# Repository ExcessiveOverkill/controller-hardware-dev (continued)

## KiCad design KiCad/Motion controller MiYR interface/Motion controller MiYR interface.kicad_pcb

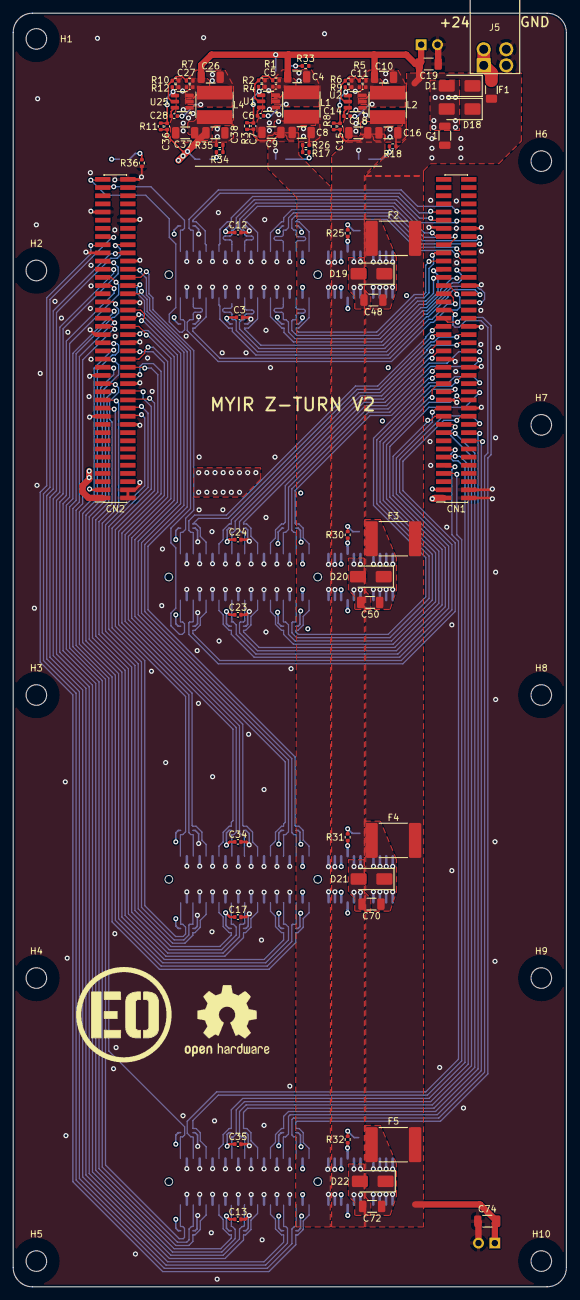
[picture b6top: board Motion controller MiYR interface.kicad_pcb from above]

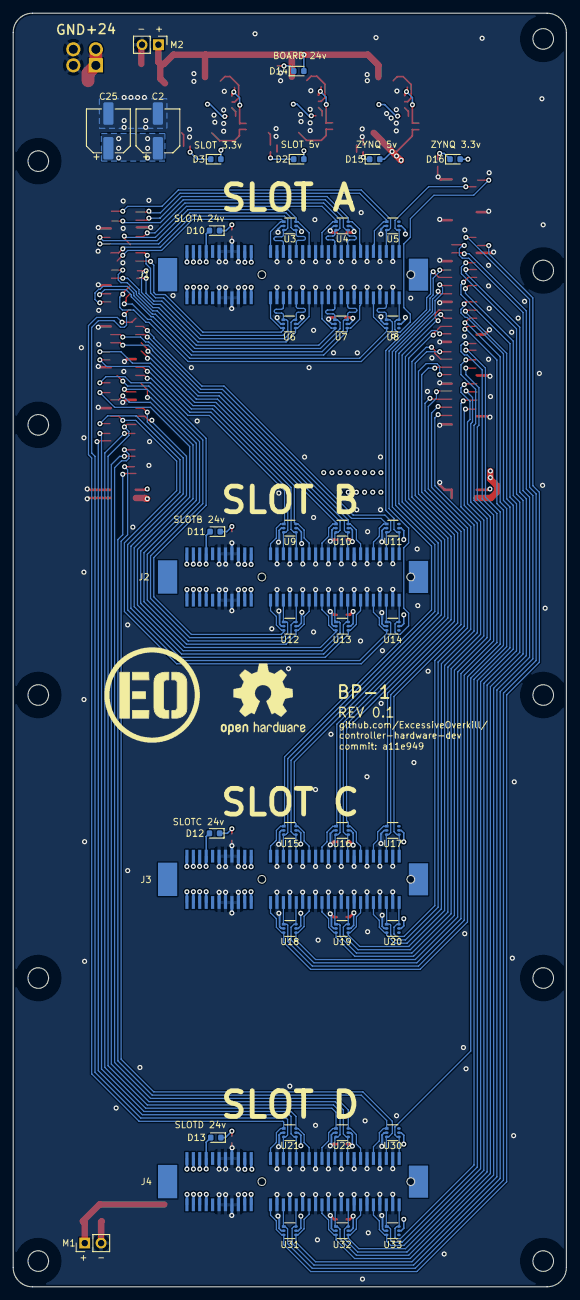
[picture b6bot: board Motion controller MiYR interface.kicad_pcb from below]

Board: 4 copper layers, 86.0 x 198.0 mm, 127 parts (41 on the bottom side), 122 nets.

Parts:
C1, C19, C48, C50, C70, C72, C74: 10uf; C_1206_3216Metric
C2, C25: 100uf; CP_Elec_6.3x7.7
C3, C5, C6, C11, C12, C13, C14, C17, C23, C24, C27, C28, C34, C35: .1uf; C_0402_1005Metric
C4, C8, C9, C10, C16, C18, C26, C37, C38: 22uf; C_1206_3216Metric
C7, C36: 75pf; C_0402_1005Metric
C15: 56pf; C_0402_1005Metric
CN1, CN2: Conn_02x40_Odd_Even; PinHeader_2x40_P1.27mm_Vertical_SMD_FLIPPED
D1, D18, D19, D20, D21, D22: SS34; D_SMA
D2, D3, D10, D11, D12, D13, D14, D15, D16: LED; LED_0603_1608Metric
F1: 10A; Fuse_1206_3216Metric
F2, F3, F4, F5: 3A; Fuse_2920_7451Metric
H1, H2, H3, H4, H5, H6, H7, H8, H9, H10: MountingHole; MountingHole_3.2mm_M3
J1, J2, J3, J4: 10061913-111PLF; PCI_64_SMD_CONNECTOR
J5: 24v; 2x02_P3.5_KF2EDGSR
L1, L2, L4: 15uH; CY54_INDUCTOR
M1, M2: Fan; PinHeader_1x02_P2.54mm_Vertical
R1, R5, R7: 500k; R_0402_1005Metric
R2, R3, R6, R8, R10, R11: 100k; R_0402_1005Metric
R4, R12, R25, R30, R31, R32, R33: 13.3k; R_0402_1005Metric
R9: 22.1k; R_0402_1005Metric
R17, R18, R26, R34, R35, R36: 1k; R_0402_1005Metric
U1, U2, U25: TPS54202DDC; SOT-23-6
U3, U4, U5, U6, U7, U8, U9, U10, U11, U12, U13, U14, U15, U16, U17, U18, U19, U20, U21, U22, U30, U31, U32, U33: D1213A-04S-7; SOT-363_DIO

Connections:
+3.3V: C3.1, C12.1, C13.1, C17.1, C23.1, C24.1, C34.1, C35.1, CN1.3, CN2.3, D16.2 (A), U3.5 (VCC), U4.5 (VCC), U5.5 (VCC), U6.5 (VCC), U7.5 (VCC), U8.5 (VCC), U9.5 (VCC), U10.5 (VCC), U11.5 (VCC), U12.5 (VCC), U13.5 (VCC), U14.5 (VCC), U15.5 (VCC), U16.5 (VCC), U17.5 (VCC), U18.5 (VCC), U19.5 (VCC), U20.5 (VCC), U21.5 (VCC), U22.5 (VCC), U30.5 (VCC), U31.5 (VCC), U32.5 (VCC), U33.5 (VCC)
+3.3VA: C15.2, C16.2, C18.2, D3.2 (A), J1.P$A10 (A10), J1.P$B10 (B10), J2.P$A10 (A10), J2.P$B10 (B10), J3.P$A10 (A10), J3.P$B10 (B10), J4.P$A10 (A10), J4.P$B10 (B10), L2.2, R8.2
+5V: C36.2, C37.2, C38.2, CN1.1, CN2.1, D15.2 (A), L4.2, R11.2
+5VA: C7.2, C8.2, C9.2, D2.2 (A), J1.P$A11 (A11), J1.P$B11 (B11), J2.P$A11 (A11), J2.P$B11 (B11), J3.P$A11 (A11), J3.P$B11 (B11), J4.P$A11 (A11), J4.P$B11 (B11), L1.2, R3.2
+24V: C1.1, C2.1, C4.2, C5.2, C10.2, C11.2, C19.1, C25.1, C26.2, C27.2, C74.1, D1.1 (K), D14.2 (A), D18.1 (K), F1.2, F2.1, F3.1, F4.1, F5.1, M1.1 (+), M2.1 (+), R1.2, R5.2, R7.2, U1.3 (VIN), U2.3 (VIN), U25.3 (VIN)
GND: C1.2, C2.2, C3.2, C4.1, C5.1, C8.1, C9.1, C10.1, C11.1, C12.2, C13.2, C16.1, C17.2, C18.1, C19.2, C23.2, C24.2, C25.2, C26.1, C27.1, C34.2, C35.2, C37.1, C38.1, C48.2, C50.2, C70.2, C72.2, C74.2, CN1.2, CN1.4, CN1.24, CN1.25, CN1.34, CN1.35, CN1.44, CN1.54, CN1.67, CN1.68, CN2.2, CN2.4, CN2.20, CN2.21, CN2.30, CN2.31, CN2.40, CN2.41, CN2.50, CN2.60, CN2.61, CN2.70, CN2.71, CN2.80, D1.2 (A), D18.2 (A), D19.2 (A), D20.2 (A), D21.2 (A), D22.2 (A), J1.P$A6 (A6), J1.P$A7 (A7), J1.P$A8 (A8), J1.P$A9 (A9), J1.P$A13 (A13), J1.P$A15 (A15), J1.P$A17 (A17), J1.P$A19 (A19), J1.P$A21 (A21), J1.P$A23 (A23), J1.P$A25 (A25), J1.P$A27 (A27), J1.P$A29 (A29), J1.P$A31 (A31), J1.P$B6 (B6), J1.P$B7 (B7), J1.P$B8 (B8), J1.P$B9 (B9), J1.P$B13 (B13), J1.P$B15 (B15), J1.P$B17 (B17), J1.P$B19 (B19), J1.P$B21 (B21), J1.P$B23 (B23), J1.P$B25 (B25), J1.P$B27 (B27), J1.P$B29 (B29), J1.P$B31 (B31), J2.P$A6 (A6), J2.P$A7 (A7), J2.P$A8 (A8), J2.P$A9 (A9), J2.P$A13 (A13), J2.P$A15 (A15), J2.P$A17 (A17), J2.P$A19 (A19), J2.P$A21 (A21), J2.P$A23 (A23), J2.P$A25 (A25), J2.P$A27 (A27), J2.P$A29 (A29), J2.P$A31 (A31), J2.P$B6 (B6), J2.P$B7 (B7), J2.P$B8 (B8), J2.P$B9 (B9), J2.P$B13 (B13), J2.P$B15 (B15), J2.P$B17 (B17), J2.P$B19 (B19), J2.P$B21 (B21), J2.P$B23 (B23), J2.P$B25 (B25), J2.P$B27 (B27), J2.P$B29 (B29), J2.P$B31 (B31), J3.P$A6 (A6), J3.P$A7 (A7), J3.P$A8 (A8), J3.P$A9 (A9), J3.P$A13 (A13), J3.P$A15 (A15), J3.P$A17 (A17), J3.P$A19 (A19), J3.P$A21 (A21), J3.P$A23 (A23), J3.P$A25 (A25), J3.P$A27 (A27), J3.P$A29 (A29), J3.P$A31 (A31), J3.P$B6 (B6), J3.P$B7 (B7), J3.P$B8 (B8), J3.P$B9 (B9), J3.P$B13 (B13), J3.P$B15 (B15), J3.P$B17 (B17), J3.P$B19 (B19), J3.P$B21 (B21), J3.P$B23 (B23), J3.P$B25 (B25), J3.P$B27 (B27), J3.P$B29 (B29), J3.P$B31 (B31), J4.P$A6 (A6), J4.P$A7 (A7), J4.P$A8 (A8), J4.P$A9 (A9), J4.P$A13 (A13), J4.P$A15 (A15), J4.P$A17 (A17), J4.P$A19 (A19), J4.P$A21 (A21), J4.P$A23 (A23), J4.P$A25 (A25), J4.P$A27 (A27), J4.P$A29 (A29), J4.P$A31 (A31), J4.P$B6 (B6), J4.P$B7 (B7), J4.P$B8 (B8), J4.P$B9 (B9), J4.P$B13 (B13), J4.P$B15 (B15), J4.P$B17 (B17), J4.P$B19 (B19), J4.P$B21 (B21), J4.P$B23 (B23), J4.P$B25 (B25), J4.P$B27 (B27), J4.P$B29 (B29), J4.P$B31 (B31), J5.3, J5.4, M1.2 (-), M2.2 (-), R2.1, R4.1, R6.1, R9.1, R10.1, R12.1, R18.1, R25.1, R26.1, R30.1, R31.1, R32.1, R33.1, R35.1, R36.1, U1.1 (GND), U2.1 (GND), U3.2 (GND), U4.2 (GND), U5.2 (GND), U6.2 (GND), U7.2 (GND), U8.2 (GND), U9.2 (GND), U10.2 (GND), U11.2 (GND), U12.2 (GND), U13.2 (GND), U14.2 (GND), U15.2 (GND), U16.2 (GND), U17.2 (GND), U18.2 (GND), U19.2 (GND), U20.2 (GND), U21.2 (GND), U22.2 (GND), U25.1 (GND), U30.2 (GND), U31.2 (GND), U32.2 (GND), U33.2 (GND)
unnamed: D2.1 (K), R17.2
unnamed: D3.1 (K), R18.2
unnamed: D10.1 (K), R25.2
unnamed: D11.1 (K), R30.2
unnamed: D12.1 (K), R31.2
unnamed: D13.1 (K), R32.2
unnamed: D14.1 (K), R33.2
unnamed: D15.1 (K), R34.2
unnamed: D16.1 (K), R36.2
unnamed: F1.1, J5.1, J5.2
unnamed: R17.1, R26.2
unnamed: R34.1, R35.2
unnamed: C6.1, U1.6 (BOOT)
unnamed: R1.1, R2.2, U1.5 (EN)
unnamed: C7.1, R3.1, R4.2, U1.4 (FB)
unnamed: C6.2, L1.1, U1.2 (SW)
unnamed: C14.1, U2.6 (BOOT)
unnamed: R5.1, R6.2, U2.5 (EN)
unnamed: C15.1, R8.1, R9.2, U2.4 (FB)
unnamed: C14.2, L2.1, U2.2 (SW)
unnamed: C28.1, U25.6 (BOOT)
unnamed: R7.1, R10.2, U25.5 (EN)
unnamed: C36.1, R11.1, R12.2, U25.4 (FB)
unnamed: C28.2, L4.1, U25.2 (SW)
SLOT A 24V: C48.1, D10.2 (A), D19.1 (K), F2.2, J1.P$A1 (A1), J1.P$A2 (A2), J1.P$A3 (A3), J1.P$A4 (A4), J1.P$B1 (B1), J1.P$B2 (B2), J1.P$B3 (B3), J1.P$B4 (B4)
SLOT B 24V: C50.1, D11.2 (A), D20.1 (K), F3.2, J2.P$A1 (A1), J2.P$A2 (A2), J2.P$A3 (A3), J2.P$A4 (A4), J2.P$B1 (B1), J2.P$B2 (B2), J2.P$B3 (B3), J2.P$B4 (B4)
SLOT C 24V: C70.1, D12.2 (A), D21.1 (K), F4.2, J3.P$A1 (A1), J3.P$A2 (A2), J3.P$A3 (A3), J3.P$A4 (A4), J3.P$B1 (B1), J3.P$B2 (B2), J3.P$B3 (B3), J3.P$B4 (B4)
SLOT D 24V: C72.1, D13.2 (A), D22.1 (K), F5.2, J4.P$A1 (A1), J4.P$A2 (A2), J4.P$A3 (A3), J4.P$A4 (A4), J4.P$B1 (B1), J4.P$B2 (B2), J4.P$B3 (B3), J4.P$B4 (B4)
SLOTA1N: CN1.62, J1.P$A14 (A14), U3.3 (CH2)
SLOTA1P: CN1.60, J1.P$A12 (A12), U3.1 (CH1)
SLOTA2N: CN1.66, J1.P$A18 (A18), U3.6 (CH4)
SLOTA2P: CN1.64, J1.P$A16 (A16), U3.4 (CH3)
SLOTA3N: CN1.65, J1.P$A22 (A22), U4.3 (CH2)
SLOTA3P: CN1.63, J1.P$A20 (A20), U4.1 (CH1)
SLOTA4N: CN1.69, J1.P$A26 (A26), U4.6 (CH4)
SLOTA4P: CN1.70, J1.P$A24 (A24), U4.4 (CH3)
SLOTA5N: CN1.72, J1.P$A30 (A30), U5.3 (CH2)
SLOTA5P: CN1.71, J1.P$A28 (A28), U5.1 (CH1)
SLOTA6N: CN1.61, J1.P$B14 (B14), U6.1 (CH1)
SLOTA6P: CN1.59, J1.P$B12 (B12), U6.3 (CH2)
SLOTA7N: CN1.57, J1.P$B18 (B18), U6.4 (CH3)
SLOTA7P: CN1.55, J1.P$B16 (B16), U6.6 (CH4)
SLOTA8N: CN1.58, J1.P$B22 (B22), U7.1 (CH1)
SLOTA8P: CN1.56, J1.P$B20 (B20), U7.3 (CH2)
SLOTA9N: CN1.52, J1.P$B26 (B26), U7.4 (CH3)
SLOTA9P: CN1.50, J1.P$B24 (B24), U7.6 (CH4)
SLOTA10N: CN1.53, J1.P$B30 (B30), U8.1 (CH1)
SLOTA10P: CN1.51, J1.P$B28 (B28), U8.3 (CH2)
SLOTA11N: CN2.79, J1.P$B32 (B32), U8.6 (CH4)
SLOTA11P: CN2.77, J1.P$A32 (A32), U5.4 (CH3)
SLOTB1N: CN1.33, J2.P$A14 (A14), U9.3 (CH2)
SLOTB1P: CN1.31, J2.P$A12 (A12), U9.1 (CH1)
SLOTB2N: CN1.38, J2.P$A18 (A18), U9.6 (CH4)
SLOTB2P: CN1.36, J2.P$A16 (A16), U9.4 (CH3)
SLOTB3N: CN1.39, J2.P$A22 (A22), U10.3 (CH2)
SLOTB3P: CN1.37, J2.P$A20 (A20), U10.1 (CH1)
SLOTB4N: CN1.42, J2.P$A26 (A26), U10.6 (CH4)
SLOTB4P: CN1.40, J2.P$A24 (A24), U10.4 (CH3)
SLOTB5N: CN1.43, J2.P$A30 (A30), U11.3 (CH2)
SLOTB5P: CN1.41, J2.P$A28 (A28), U11.1 (CH1)
SLOTB6N: CN1.32, J2.P$B14 (B14), U12.1 (CH1)
SLOTB6P: CN1.30, J2.P$B12 (B12), U12.3 (CH2)
SLOTB7N: CN1.29, J2.P$B18 (B18), U12.4 (CH3)
SLOTB7P: CN1.27, J2.P$B16 (B16), U12.6 (CH4)
SLOTB8N: CN1.28, J2.P$B22 (B22), U13.1 (CH1)
SLOTB8P: CN1.26, J2.P$B20 (B20), U13.3 (CH2)
SLOTB9N: CN1.23, J2.P$B26 (B26), U13.4 (CH3)
SLOTB9P: CN1.21, J2.P$B24 (B24), U13.6 (CH4)
SLOTB10N: CN1.22, J2.P$B30 (B30), U14.1 (CH1)
SLOTB10P: CN1.20, J2.P$B28 (B28), U14.3 (CH2)
SLOTB11N: CN2.58, J2.P$B32 (B32), U14.6 (CH4)
SLOTB11P: CN2.56, J2.P$A32 (A32), U11.4 (CH3)
SLOTC1N: CN2.54, J3.P$A14 (A14), U15.3 (CH2)
SLOTC1P: CN2.52, J3.P$A12 (A12), U15.1 (CH1)
SLOTC2N: CN2.48, J3.P$A18 (A18), U15.6 (CH4)
SLOTC2P: CN2.46, J3.P$A16 (A16), U15.4 (CH3)
SLOTC3N: CN2.44, J3.P$A22 (A22), U16.3 (CH2)
SLOTC3P: CN2.42, J3.P$A20 (A20), U16.1 (CH1)
SLOTC4N: CN2.38, J3.P$A26 (A26), U16.6 (CH4)
SLOTC4P: CN2.36, J3.P$A24 (A24), U16.4 (CH3)
SLOTC5N: CN2.34, J3.P$A30 (A30), U17.3 (CH2)
SLOTC5P: CN2.32, J3.P$A28 (A28), U17.1 (CH1)
SLOTC6N: CN2.39, J3.P$B14 (B14), U18.1 (CH1)
SLOTC6P: CN2.37, J3.P$B12 (B12), U18.3 (CH2)
SLOTC7N: CN2.35, J3.P$B18 (B18), U18.4 (CH3)
SLOTC7P: CN2.33, J3.P$B16 (B16), U18.6 (CH4)
SLOTC8N: CN2.29, J3.P$B22 (B22), U19.1 (CH1)
SLOTC8P: CN2.27, J3.P$B20 (B20), U19.3 (CH2)
SLOTC9N: CN2.25, J3.P$B26 (B26), U19.4 (CH3)
SLOTC9P: CN2.23, J3.P$B24 (B24), U19.6 (CH4)
SLOTC10N: CN2.24, J3.P$B30 (B30), U20.1 (CH1)
SLOTC10P: CN2.22, J3.P$B28 (B28), U20.3 (CH2)
SLOTC11N: CN2.28, J3.P$B32 (B32), U20.6 (CH4)
SLOTC11P: CN2.26, J3.P$A32 (A32), U17.4 (CH3)
SLOTD1N: CN1.47, J4.P$A14 (A14), U21.3 (CH2)
SLOTD1P: CN1.45, J4.P$A12 (A12), U21.1 (CH1)
SLOTD2N: CN1.18, J4.P$A18 (A18), U21.6 (CH4)
SLOTD2P: CN1.16, J4.P$A16 (A16), U21.4 (CH3)
SLOTD3N: CN1.19, J4.P$A22 (A22), U22.3 (CH2)
SLOTD3P: CN1.17, J4.P$A20 (A20), U22.1 (CH1)
SLOTD4N: CN1.13, J4.P$A26 (A26), U22.6 (CH4)
SLOTD4P: CN1.11, J4.P$A24 (A24), U22.4 (CH3)
SLOTD5N: CN1.9, J4.P$A30 (A30), U30.3 (CH2)
SLOTD5P: CN1.7, J4.P$A28 (A28), U30.1 (CH1)
SLOTD6N: CN2.65, J4.P$B14 (B14), U31.1 (CH1)
SLOTD6P: CN2.63, J4.P$B12 (B12), U31.3 (CH2)
SLOTD7N: CN2.64, J4.P$B18 (B18), U31.4 (CH3)
SLOTD7P: CN2.62, J4.P$B16 (B16), U31.6 (CH4)
SLOTD8N: CN2.59, J4.P$B22 (B22), U32.1 (CH1)
SLOTD8P: CN2.57, J4.P$B20 (B20), U32.3 (CH2)
SLOTD9N: CN2.55, J4.P$B26 (B26), U32.4 (CH3)
SLOTD9P: CN2.53, J4.P$B24 (B24), U32.6 (CH4)
SLOTD10N: CN2.49, J4.P$B30 (B30), U33.1 (CH1)
SLOTD10P: CN2.47, J4.P$B28 (B28), U33.3 (CH2)
SLOTD11N: CN2.45, J4.P$B32 (B32), U33.6 (CH4)
SLOTD11P: CN2.43, J4.P$A32 (A32), U30.4 (CH3)

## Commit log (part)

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2026-01-11 add modular boards
2026-01-15 update boards
2026-01-15 fix jumper
2026-05-09 work on serial module
